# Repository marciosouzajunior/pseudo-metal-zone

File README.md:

# Pseudo Metal Zone

Pedal de distorção/fuzz pesado baseado em **RC4558/JRC4558**, desenvolvido em protoboard e depois convertido para **PCB V1 em KiCad**.

A ideia é chegar em uma distorção agressiva para baixo/guitarra, inspirada de forma conceitual no Boss Metal Zone e em timbres de hard rock/nu metal, mas com um circuito simples, compreendido estágio por estágio, usando componentes THT e um único CI dual op-amp.

## Objetivo sonoro

- Distorção pesada para baixo/guitarra.
- Mais definida que fuzz puro.
- Grave presente, mas sem embolar demais.
- Agudos controlados, reduzindo fizz/chiado.
- Funcionamento com alimentação simples de 9 V.
- Projeto didático, fácil de modificar e medir.

## Arquitetura do circuito

Fluxo geral do sinal:

```text
INPUT
→ C_INPUT_COUPLING
→ GAIN STAGE A
→ C_INTERSTAGE
→ GAIN STAGE B
→ C_CLIP_IN
→ ASYMMETRICAL CLIPPING
→ ANTI-FIZZ
→ MASTER VOLUME
→ C_OUTPUT_COUPLING
→ OUTPUT
```

## Alimentação e referência

### Alimentação

```text
Jack DC 9 V → chave SPST → +9V
```

- Fonte: 9 V DC.
- CI: RC4558/JRC4558.
- Pino 8 do 4558: +9 V.
- Pino 4 do 4558: GND.
- O circuito usa alimentação simples, então os estágios de áudio trabalham referenciados em VREF.

### Filtro principal

```text
+9V → C_POWER_FILTER 100uF → GND
```

Função: reduzir ruído/ripple da alimentação e estabilizar a linha de 9 V.

### VREF

```text
+9V
→ R_VREF_TOP 100k
→ VREF
→ R_VREF_BOTTOM 100k
→ GND
```

```text
VREF → C_VREF_FILTER 100uF → GND
```

- VREF esperado: aproximadamente 4,5 V.
- Inicialmente foi usado 1000 uF no VREF; funcionou, mas demorava mais para estabilizar e o áudio demorava a aparecer ao ligar.
- Valor atual escolhido: **100 uF**.

### Desacoplamento do op-amp

```text
pino 8 → C_OPAMP_DECOUPLING 100nF (104) → pino 4
```

Deve ficar fisicamente o mais próximo possível do RC4558.

## Entrada

```text
INPUT → C_INPUT_COUPLING 100nF (104) → pino 3
pino 3 → R_INPUT_BIAS 1M → VREF
```

Funções:

- `C_INPUT_COUPLING`: bloqueia DC e deixa o áudio passar.
- `R_INPUT_BIAS`: polariza a entrada em VREF e mantém alta impedância.

## Estágio A

Primeiro estágio de ganho, usando a primeira metade do 4558.

```text
pino 1 → R_STAGE1_GAIN 100k → pino 2
pino 2 → R_STAGE1_REF 4.7k → VREF
```

Onde:

- `R_STAGE1_GAIN` (100k): resistor de realimentação (feedback).
- `R_STAGE1_REF` (4.7k): resistor de referência que define o ganho junto com R_STAGE1_GAIN.

Ganho aproximado:

```text
R_STAGE1_GAIN / R_STAGE1_REF = 100k / 4.7k ≈ 22x
```

Função:

- Pré-amplificar o sinal.
- Preparar o sinal para o segundo estágio.
- Gerar drive inicial sem deixar o circuito totalmente fora de controle.

## Filtro entre estágios

```text
pino 1 → C_INTERSTAGE → pino 5
pino 5 → R_STAGE2_BIAS 100k → VREF
```

Valor escolhido:

```text
C_INTERSTAGE = 10nF (103)
```

Essa foi uma das mudanças mais importantes do projeto. O 103 cortou parte dos graves antes do segundo estágio, deixando o som mais definido e agressivo. O 104 ficou mais cheio/aberto, mas menos controlado. O 153 ficou no meio do caminho.

## Estágio B

Estágio principal de ganho, usando a segunda metade do 4558.

```text
pino 7 ↔ P_GAIN 100k ↔ pino 6
pino 6 → R_STAGE2_REF 22k → VREF
R_LIMIT_GAIN 47k em paralelo com P_GAIN
```

Ligação robusta sugerida do pot como reostato:

```text
terminal 2 e 3 unidos
terminal 1 no pino 6
```

O resistor `R_LIMIT_GAIN` em paralelo com o potenciômetro limita o ganho máximo e evita que a onda colapse ou fique irregular demais. Foram testados 22k e 47k; ambos funcionaram, com preferência atual por **47k**.

## Pré-clipping

```text
pino 7 → C_CLIP_IN → CLIP_NODE
```

Valor atual:

```text
C_CLIP_IN = 220nF (224 ou u22)
```

Função:

- Moldar o corpo do sinal antes dos diodos.
- Controlar quanto grave chega ao clipping.

Testes mostraram que 224 trouxe mais corpo e graves do que 104, mantendo uma resposta ainda utilizável.

## Clipping assimétrico

Configuração atual:

```text
CLIP_NODE
├─ 1 diodo 1N4148 para GND em um sentido
└─ 2 diodos 1N4148 em série para GND no sentido oposto
```

Função:

- Gerar a distorção principal.
- Produzir clipping assimétrico.
- Criar harmônicos mais ricos que a clipagem perfeitamente simétrica.

Comparações feitas:

- Sem diodos: o op-amp clipa por saturação em ganho alto, mas o resultado depende muito do nível de entrada.
- 2 diodos antiparalelos: clipping simétrico, visível e funcional.
- 3 diodos assimétricos: resultado favorito, mais interessante e menos “reto”.

## Anti-fizz

```text
CLIP_NODE → R_FIZZ 10k → OUTPUT_FILTER
OUTPUT_FILTER → C_FIZZ 3n3 → GND
```

Função:

- Reduzir agudos ásperos depois do clipping.
- Controlar fizz/chiado.
- Suavizar frequências altas sem matar totalmente a definição.

Configuração atual:

```text
R_FIZZ = 10k
C_FIZZ = 3n3
```

## Volume master e saída

```text
OUTPUT_FILTER → P_VOLUME 100k → C_OUTPUT_COUPLING 1uF → OUTPUT
```

Ligação típica do volume:

```text
terminal 1 = sinal
terminal 3 = GND
terminal 2 = saída
```

`C_OUTPUT_COUPLING = 1uF` foi mantido na V1 para bloquear DC residual antes do jack de saída.

## Indicação e proteção

### LED de indicação de energia

```text
+9V → R_LED 2.2k → LED_POWER → GND
```

Função:

- Indicar que o pedal está ligado.
- Proteger o LED com resistor limitador de corrente.

Valor do resistor:

- `R_LED = 2.2k` para LED típico de 5 mm com corrente limitada.
- LED escolhido: 5 mm THT, cor livre (vermelho recomendado).

## Configuração atual da PCB V1

| Bloco | Referência | Valor atual |
|---|---|---|
| **Fonte e referência** | | |
| CI principal | U1 | RC4558/JRC4558 DIP-8 + soquete |
| Alimentação | — | 9 V DC |
| Filtro de alimentação | C_POWER_FILTER | 100uF eletrolítico |
| VREF divisor | R_VREF_TOP / R_VREF_BOTTOM | 100k / 100k |
| Filtro VREF | C_VREF_FILTER | 100uF eletrolítico |
| Desacoplamento CI | C_OPAMP_DECOUPLING | 100nF (104) cerâmico |
| **Entrada** | | |
| Acoplamento entrada | C_INPUT_COUPLING | 100nF (104) filme P5mm |
| Bias entrada | R_INPUT_BIAS | 1M |
| **Estágio A** | | |
| Realimentação | R_STAGE1_GAIN | 100k |
| Referência | R_STAGE1_REF | 4.7k |
| **Interstage** | | |
| Filtro interstage | C_INTERSTAGE | 10nF (103) filme P5mm |
| Bias estágio B | R_STAGE2_BIAS | 100k |
| **Estágio B** | | |
| Ganho | P_GAIN | 100k potenciômetro linear |
| Limitador ganho | R_LIMIT_GAIN | 47k em paralelo com P_GAIN |
| Referência | R_STAGE2_REF | 22k |
| **Clipping** | | |
| Pré-clipping | C_CLIP_IN | 220nF (224) filme P5mm |
| Diodos clipping | D_CLIP_A, D_CLIP_B, D_CLIP_C | 3x 1N4148 assimétricos |
| **Anti-fizz** | | |
| Resistor anti-fizz | R_FIZZ | 10k |
| Capacitor anti-fizz | C_FIZZ | 3.3nF (3n3) filme P5mm |
| **Volume e saída** | | |
| Volume master | P_VOLUME | 100k potenciômetro log |
| Acoplamento saída | C_OUTPUT_COUPLING | 1uF eletrolítico |
| **Indicação** | | |
| LED indicador | LED_POWER | 5mm THT |
| Resistor LED | R_LED | 2.2k |

## Conectividade externa

A PCB V1 usa **headers e fios** para conexão de componentes externos:

- **DC_IN**: entrada de alimentação (9V DC) com chave.
- **INPUT**: jack de entrada de áudio.
- **OUTPUT**: jack de saída de áudio.
- **P_GAIN**: potenciômetro de ganho do estágio B (100k linear).
- **P_VOLUME**: potenciômetro de volume master (100k logarítmico).
- **Pads opcionais**: diversos pads de teste e pontos de modificação (13 pads 1x01).

Vide `docs/BOM.md` para detalhes de footprints e conexões.

## Principais descobertas

- Dois estágios funcionaram melhor que um único estágio.
- Ganho excessivo gera fuzz, compressão e perda de definição.
- O filtro entre estágios foi a alteração mais importante para definição.
- O anti-fizz reduziu significativamente o chiado/fizz dos agudos.
- Três diodos assimétricos soaram melhor que dois diodos simétricos.
- O sweet spot do ganho ficou baixo, aproximadamente entre 20% e 35% do pot em alguns testes.
- Abrir demais o ganho não significa necessariamente som melhor; em alguns pontos a onda fica irregular e a medição cai por compressão/limitação.
- O celular em 50% gera sinal mais forte e mais previsível que o baixo, então é bom para comparar medições, mas o instrumento real continua sendo a referência sonora final.
- O RC4558 sozinho consegue clipar por saturação quando há ganho suficiente.
- O TL072 foi testado, mas não trouxe vantagem imediata nesta fase.

## Resumo das medições principais

As medições completas estão em [docs/MEASUREMENTS.md](docs/MEASUREMENTS.md).

### Filtro entre estágios

Configuração:

```text
pino 1 → capacitor → pino 5
pino 5 → 100k → VREF
```

| Capacitor | 80 Hz | 120 Hz | 220 Hz | 440 Hz | 880 Hz | Resultado |
|---|---:|---:|---:|---:|---:|---|
| 104 | 0.0982 | 0.1110 | 0.1185 | 0.0876 | 0.0842 | mais grave/aberto |
| 153 | 0.0613 | 0.0852 | 0.1073 | 0.0851 | 0.0834 | intermediário |
| 103 | 0.0470 | 0.0687 | 0.0942 | 0.0804 | 0.0817 | escolhido, mais definido |

### Pré-clipping 104 vs 224

| C_CLIP_IN | 80 Hz | 120 Hz | 220 Hz | 440 Hz | 880 Hz | 2 kHz | 4 kHz | 8 kHz |
|---|---:|---:|---:|---:|---:|---:|---:|---:|
| 104 / 100nF | 0.079 | 0.091 | 0.103 | 0.102 | 0.105 | 0.098 | 0.075 | 0.053 |
| 224 / 220nF | 0.092 | 0.104 | 0.115 | 0.114 | 0.116 | 0.108 | 0.090 | 0.069 |

Resultado: **224** trouxe mais corpo e graves.

### Anti-fizz 10k + 3n3

| Frequência | Medição |
|---:|---:|
| 80 Hz | 0.086 |
| 120 Hz | 0.097 |
| 220 Hz | 0.114 |
| 440 Hz | 0.110 |
| 880 Hz | 0.114 |
| 2 kHz | 0.108 |
| 4 kHz | 0.091 |
| 8 kHz | 0.069 |

### Curva de ganho

| Potenciômetro | Medição | Observação |
|---:|---:|---|
| 0% | 0.069 | limpo |
| 25% | 0.097 | melhor ponto |
| 50% | 0.090 | deformação |
| 75% | 0.080 | irregular |
| 100% | 0.078 | irregular |

Sweet spot observado: **20% a 35%**.

## Notas resumidas de PCB

A PCB V1 foi pensada como placa experimental de face simples/THT, com alguns pontos de modificação.

- Camadas: 1.
- Dimensão aproximada: 62,65 mm × 61,8 mm.
- O silk fica do lado dos componentes.
- Jumpers podem cruzar trilhas, mas devem ser feitos com fio isolado quando passarem por cima de cobre/trilhas.
- Jumpers no lado dos componentes não devem encostar em trilhas expostas.
- Conferir especialmente jumpers que cruzam VREF, +9V ou saídas de estágio.

### Estratégia de layout

Fluxo recomendado:

```text
INPUT → STAGE A → STAGE B → CLIP → ANTI-FIZZ → VOLUME → OUTPUT
```

Prioridades:

- RC4558 central.
- Capacitor de desacoplamento o mais perto possível do CI.
- Alimentação e VREF estáveis.
- Entrada longe da saída e de nós de alto ganho.
- Trilhas curtas nos pontos de maior ganho.
- Plano de GND quando possível.
- Evitar laços grandes.
- Conferir orientação dos diodos.
- Conferir pinos do 4558 antes de soldar.

### Footprints usados/planejados

| Componente | Footprint |
|---|---|
| RC4558 | `Package_DIP:DIP-8_W7.62mm` |
| Resistores | `R_Axial_DIN0207_P7.62mm` |
| Diodos | `D_DO35_SOD27_P7.62mm` |
| Capacitores de voicing | `C_Rect_L7.2mm_W2.5mm_P5.00mm` |
| Eletrolíticos | `CP_Radial_D5.0mm_P2.00mm` |
| Potenciômetros | Header 1x3, ligados por fios |
| Jacks | Header 1x2, ligados por fios |

### Pontos úteis de modificação/teste

- `C_INTERSTAGE`: 103 (10nF), 153 (15nF), 104 (100nF).
- `C_CLIP_IN`: 104 (100nF), 224 (220nF).
- `R_LIMIT_GAIN`: 22k, 33k, 47k, 68k.
- `C_FIZZ`: sem capacitor, 2n2 (2.2nF), 3n3 (3.3nF), 4n7 (4.7nF), 6n8 (6.8nF).
- Pads de teste para +9V, GND, VREF, saída do estágio A, entrada do estágio B, CLIP_NODE e OUTPUT.

## Arquivos do repo

```text
README.md                         documentação principal

docs/
  BOM.md                          lista de componentes da PCB V1
  MEASUREMENTS.md                 medições e testes de desenvolvimento
  PseudoMetalZone_V1_Schematic.pdf
                                  esquemático exportado em PDF
  maloyk.png                      imagem de referência/inspiração

hardware/
  PseudoMetalZone_V1.kicad_sch    esquemático do KiCad
  PseudoMetalZone_V1.kicad_pcb    layout da PCB
  PseudoMetalZone_V1.kicad_pro    arquivo do projeto
  PseudoMetalZone_V1.kicad_prl    preferências do projeto

gerbers/
  PseudoMetalZone_V1-F_Cu.gtl     cobre frente
  PseudoMetalZone_V1-B_Cu.gbl     cobre verso
  PseudoMetalZone_V1-F_Mask.gts   máscara de solda frente
  PseudoMetalZone_V1-B_Mask.gbs   máscara de solda verso
  PseudoMetalZone_V1-F_Silkscreen.gto
                                  serigrafia frente
  PseudoMetalZone_V1-B_Silkscreen.gbo
                                  serigrafia verso
  PseudoMetalZone_V1-Edge_Cuts.gm1
                                  contorno da placa
  PseudoMetalZone_V1.drl          furos (drill)
  PseudoMetalZone_V1-job.gbrjob   configuração do job
```

## Procedimentos para nova placa

1. Conferir continuidade de +9V, GND e VREF antes de inserir o CI.
2. Alimentar a placa sem o 4558 e medir:
   - +9V no pino 8 do soquete.
   - GND no pino 4 do soquete.
   - VREF próximo de 4,5 V.
3. Conferir se não há curto entre +9V e GND.
4. Inserir o 4558 no soquete.
5. Testar áudio limpo em ganho baixo.
6. Testar ganho progressivamente.
7. Medir saída do estágio A, entrada do estágio B, CLIP_NODE e saída final.
8. Testar com guitarra real e baixo real antes de decidir novas alterações.

## Decisões a serem avaliadas depois

- Se o 224 antes dos diodos será mantido definitivamente.
- Se o anti-fizz 3n3 está no ponto ideal.
- Se o resistor de limite de ganho fica em 47k ou outro valor.
- Se o pedal precisa de tone control mais elaborado.
- Se o volume master e o capacitor de saída estão com valores ideais.
- Se vale comparar novamente 4558 vs TL072 na PCB.

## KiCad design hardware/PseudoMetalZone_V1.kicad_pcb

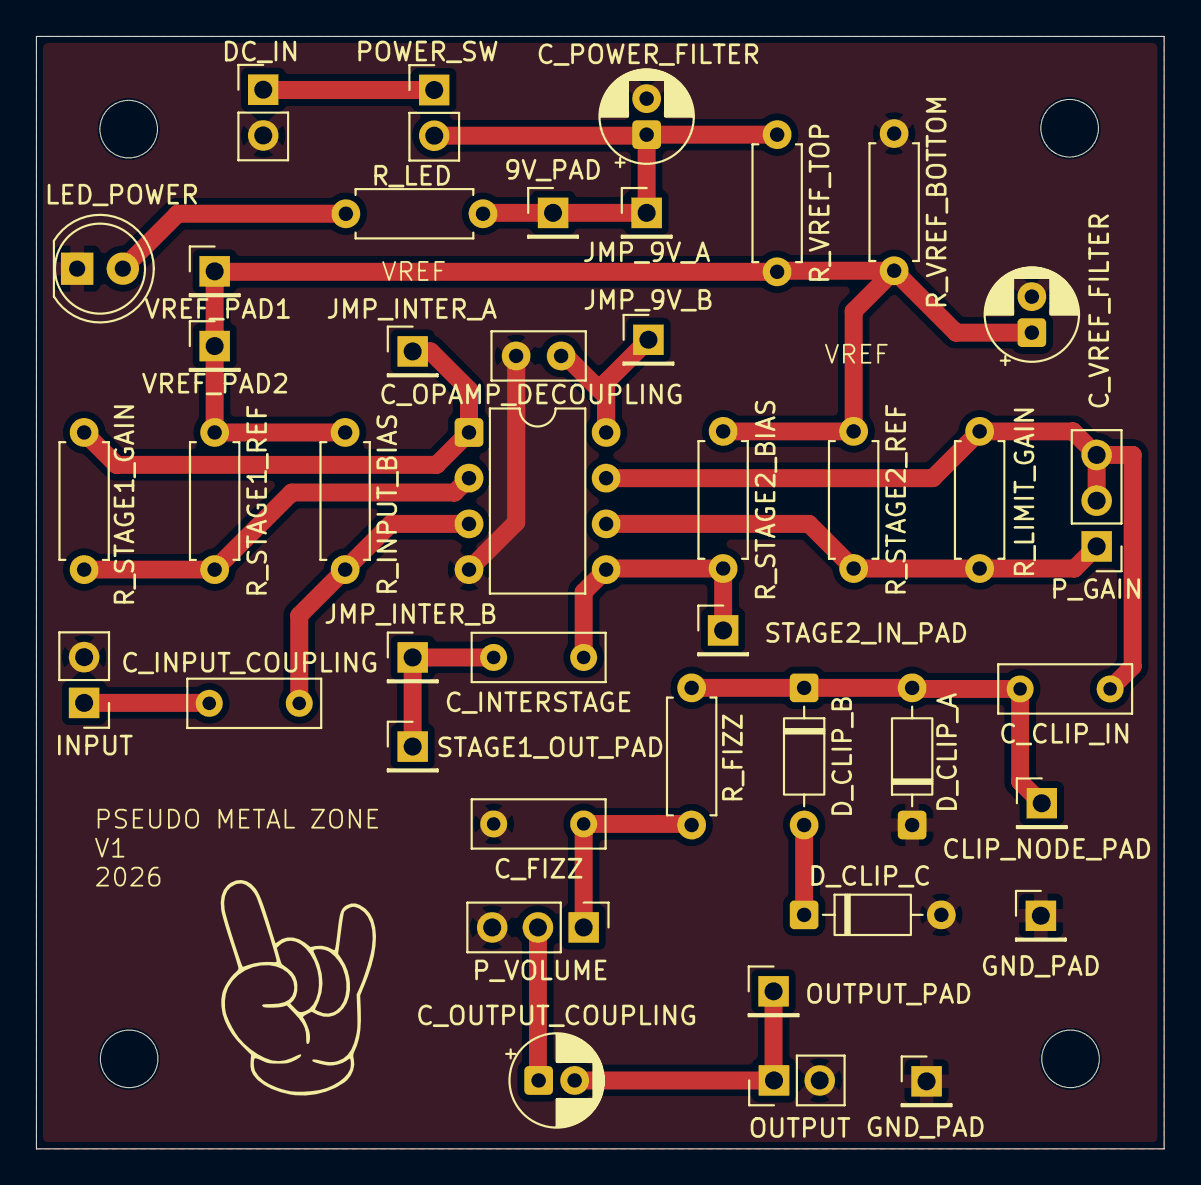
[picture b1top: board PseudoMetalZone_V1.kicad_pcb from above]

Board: 2 copper layers, 62.7 x 61.8 mm, 42 parts (0 on the bottom side), 16 nets.

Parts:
9V_PAD: Conn_01x01; PinHeader_1x01_P2.54mm_Vertical
CLIP_NODE_PAD: Conn_01x01; PinHeader_1x01_P2.54mm_Vertical
C_CLIP_IN: 220nf; C_Rect_L7.2mm_W2.5mm_P5.00mm
C_FIZZ: 3n3; C_Rect_L7.2mm_W2.5mm_P5.00mm
C_INPUT_COUPLING: 100nf; C_Rect_L7.2mm_W2.5mm_P5.00mm
C_INTERSTAGE: 10nf; C_Rect_L7.2mm_W2.5mm_P5.00mm
C_OPAMP_DECOUPLING: 100nf; C_Disc_D5.0mm_W2.5mm_P2.50mm
C_OUTPUT_COUPLING: 1uf; CP_Radial_D5.0mm_P2.00mm
C_POWER_FILTER: 100uf; CP_Radial_D5.0mm_P2.00mm
C_VREF_FILTER: 100uf; CP_Radial_D5.0mm_P2.00mm
DC_IN: POWER_SW; PinHeader_1x02_P2.54mm_Vertical
D_CLIP_A: 1N4148; D_DO-35_SOD27_P7.62mm_Horizontal
D_CLIP_B: 1N4148; D_DO-35_SOD27_P7.62mm_Horizontal
D_CLIP_C: 1N4148; D_DO-35_SOD27_P7.62mm_Horizontal
GND_PAD: Conn_01x01; PinHeader_1x01_P2.54mm_Vertical
GND_PAD#2: Conn_01x01; PinHeader_1x01_P2.54mm_Vertical
INPUT: PinHeader_1x02_P2.54mm_Vertical
JMP_9V_A, JMP_9V_B: Conn_01x01; PinHeader_1x01_P2.54mm_Vertical
JMP_INTER_A: Conn_01x01; PinHeader_1x01_P2.54mm_Vertical
JMP_INTER_B: Conn_01x01; PinHeader_1x01_P2.54mm_Vertical
LED_POWER: LED; LED_D5.0mm
OUTPUT: PinHeader_1x02_P2.54mm_Vertical
OUTPUT_PAD: Conn_01x01; PinHeader_1x01_P2.54mm_Vertical
POWER_SW: PinHeader_1x02_P2.54mm_Vertical
P_GAIN: 100k; PinHeader_1x03_P2.54mm_Vertical
P_VOLUME: 100k; PinHeader_1x03_P2.54mm_Vertical
R_FIZZ: 10k; R_Axial_DIN0207_L6.3mm_D2.5mm_P7.62mm_Horizontal
R_INPUT_BIAS: 1M; R_Axial_DIN0207_L6.3mm_D2.5mm_P7.62mm_Horizontal
R_LED: 2k2; R_Axial_DIN0207_L6.3mm_D2.5mm_P7.62mm_Horizontal
R_LIMIT_GAIN: 47k; R_Axial_DIN0207_L6.3mm_D2.5mm_P7.62mm_Horizontal
R_STAGE1_GAIN, R_STAGE2_BIAS: 100k; R_Axial_DIN0207_L6.3mm_D2.5mm_P7.62mm_Horizontal
R_STAGE1_REF: 4.7k; R_Axial_DIN0207_L6.3mm_D2.5mm_P7.62mm_Horizontal
R_STAGE2_REF: 22K; R_Axial_DIN0207_L6.3mm_D2.5mm_P7.62mm_Horizontal
R_VREF_BOTTOM: 100k; R_Axial_DIN0207_L6.3mm_D2.5mm_P7.62mm_Horizontal
R_VREF_TOP: 100k; R_Axial_DIN0207_L6.3mm_D2.5mm_P7.62mm_Horizontal
STAGE1_OUT_PAD, STAGE2_IN_PAD: Conn_01x01; PinHeader_1x01_P2.54mm_Vertical
U1: RC4558; DIP-8_W7.62mm
VREF_PAD1, VREF_PAD2: Conn_01x01; PinHeader_1x01_P2.54mm_Vertical

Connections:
+9V: 9V_PAD.1 (Pin_1_1), C_OPAMP_DECOUPLING.1, C_POWER_FILTER.1, JMP_9V_A.1 (Pin_1_1), JMP_9V_B.1 (Pin_1_1), POWER_SW.2 (B), R_LED.2, R_VREF_TOP.1, U1.8 (V+)
/CLIP_NODE: CLIP_NODE_PAD.1 (Pin_1_1), C_CLIP_IN.2, D_CLIP_A.2 (A), D_CLIP_B.1 (K), R_FIZZ.1
/INPUT: C_INPUT_COUPLING.1, C_INPUT_COUPLING.2, INPUT.1, R_INPUT_BIAS.2, U1.3 (+)
/OUTPUT: C_OUTPUT_COUPLING.1, C_OUTPUT_COUPLING.2, OUTPUT.1, OUTPUT_PAD.1 (Pin_1_1), P_VOLUME.2
/VREF: C_VREF_FILTER.1, R_INPUT_BIAS.1, R_STAGE1_REF.1, R_STAGE2_BIAS.1, R_STAGE2_REF.1, R_VREF_BOTTOM.2, R_VREF_TOP.2, VREF_PAD1.1 (Pin_1_1), VREF_PAD2.1 (Pin_1_1)
GND: C_FIZZ.2, C_OPAMP_DECOUPLING.2, C_POWER_FILTER.2, C_VREF_FILTER.2, DC_IN.2, D_CLIP_A.1 (K), D_CLIP_C.2 (A), GND_PAD.1 (Pin_1_1), GND_PAD#2.1 (Pin_1_1), INPUT.2, LED_POWER.1 (K), OUTPUT.2, P_VOLUME.3, R_VREF_BOTTOM.1, U1.4 (V-)
unnamed: C_CLIP_IN.1, P_GAIN.2, P_GAIN.3, R_LIMIT_GAIN.2, U1.7
unnamed: C_FIZZ.1, P_VOLUME.1, R_FIZZ.2
unnamed: D_CLIP_B.2 (A), D_CLIP_C.1 (K)
unnamed: JMP_INTER_A.1 (Pin_1_1), R_STAGE1_GAIN.2, U1.1
unnamed: C_INTERSTAGE.1, JMP_INTER_B.1 (Pin_1_1), STAGE1_OUT_PAD.1 (Pin_1_1)
unnamed: LED_POWER.2 (A), R_LED.1
unnamed: DC_IN.1, POWER_SW.1 (A)
unnamed: C_INTERSTAGE.2, R_STAGE2_BIAS.2, STAGE2_IN_PAD.1 (Pin_1_1), U1.5 (+)
unnamed: R_STAGE1_GAIN.1, R_STAGE1_REF.2, U1.2 (-)
unnamed: P_GAIN.1, R_LIMIT_GAIN.1, R_STAGE2_REF.2, U1.6 (-)

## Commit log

2026-06-11 Atualiza documentação do README.md e do BOM.md com informações sobre a PCB V1 e melhorias na seção de medições.
2026-06-11 Remove temporary lock file and clear used designators in PCB project file
